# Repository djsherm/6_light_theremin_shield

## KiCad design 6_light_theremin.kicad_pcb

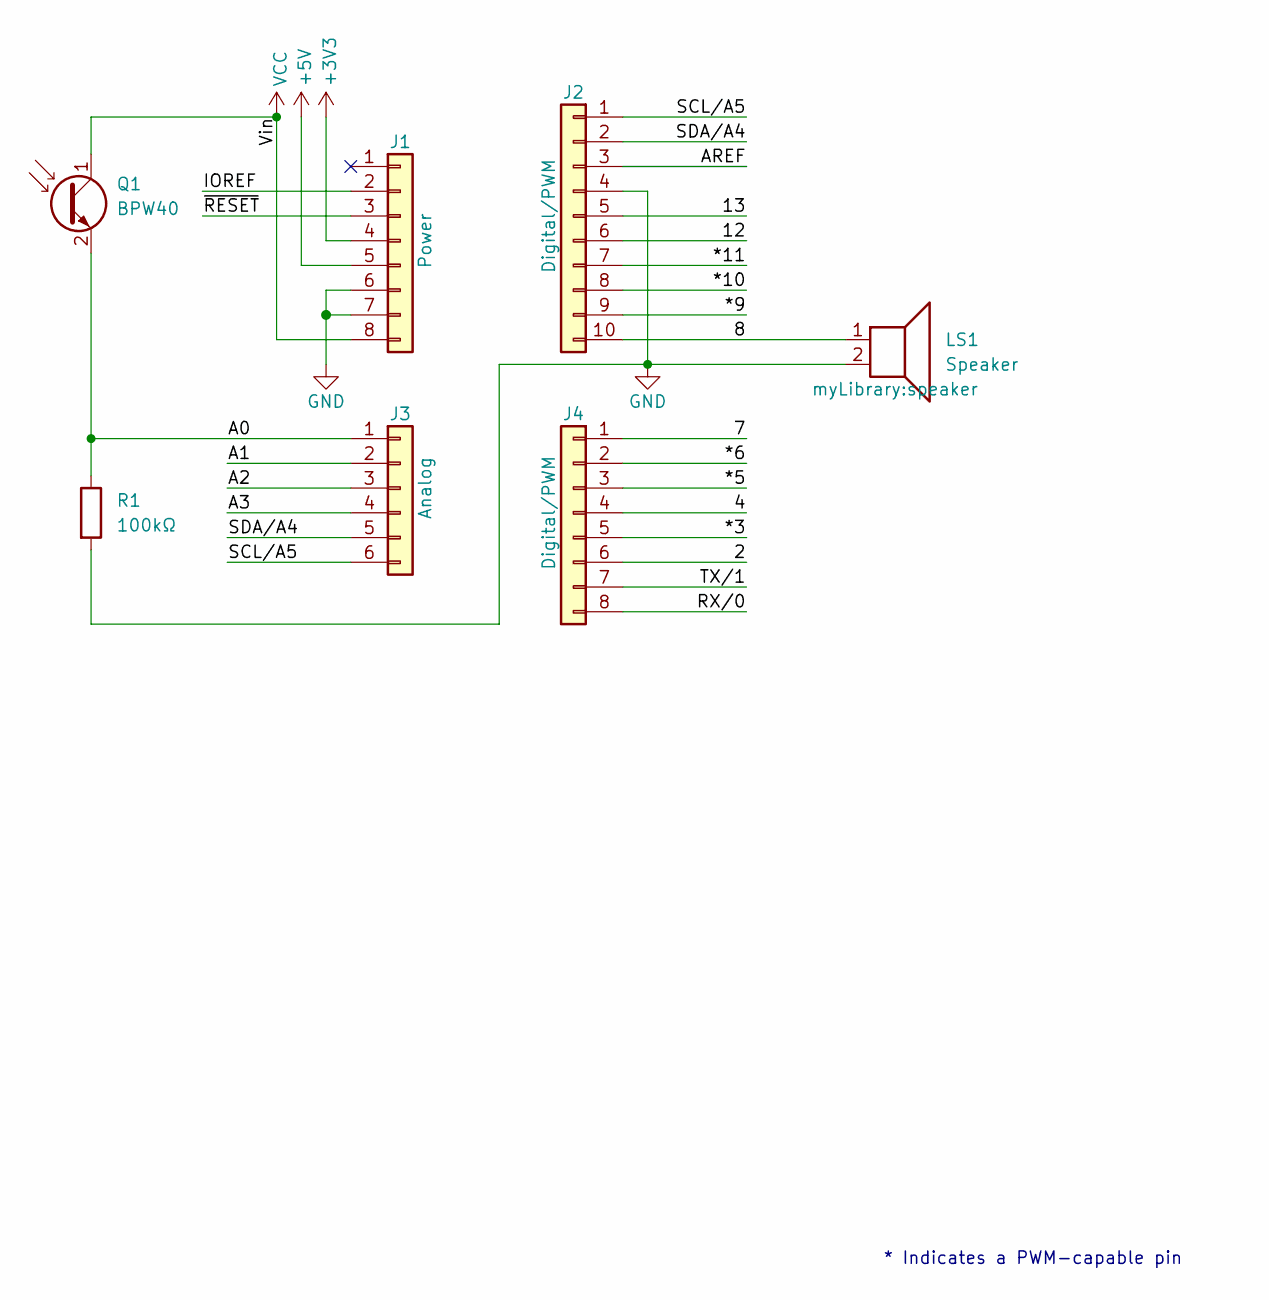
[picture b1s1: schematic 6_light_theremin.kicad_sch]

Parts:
J1: Power; PinSocket_1x08_P2.54mm_Vertical
J2: Digital/PWM; PinSocket_1x10_P2.54mm_Vertical
J3: Analog; PinSocket_1x06_P2.54mm_Vertical
J4: Digital/PWM; PinSocket_1x08_P2.54mm_Vertical
LS1: Speaker; speaker
Q1: BPW40; LED_D5.0mm_Clear
R1: 100kΩ; R_Axial_DIN0207_L6.3mm_D2.5mm_P10.16mm_Horizontal

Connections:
+3V3: J1.4
+5V: J1.5
/2: J4.6
/4: J4.4
/7: J4.1
/8: J2.10, LS1.1
/12: J2.6
/13: J2.5
/*3: J4.5
/*5: J4.3
/*6: J4.2
/*9: J2.9
/*10: J2.8
/*11: J2.7
/A0: J3.1, Q1.2 (E), R1.1
/A1: J3.2
/A2: J3.3
/A3: J3.4
/AREF: J2.3
/IOREF: J1.2
/RX/0: J4.8
/SCL/A5: J2.1, J3.6
/SDA/A4: J2.2, J3.5
/TX/1: J4.7
/~RESET: J1.3
GND: J1.6, J1.7, J2.4, LS1.2, R1.2
VCC: J1.8, Q1.1 (C)

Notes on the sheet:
* Indicates a PWM-capable pin

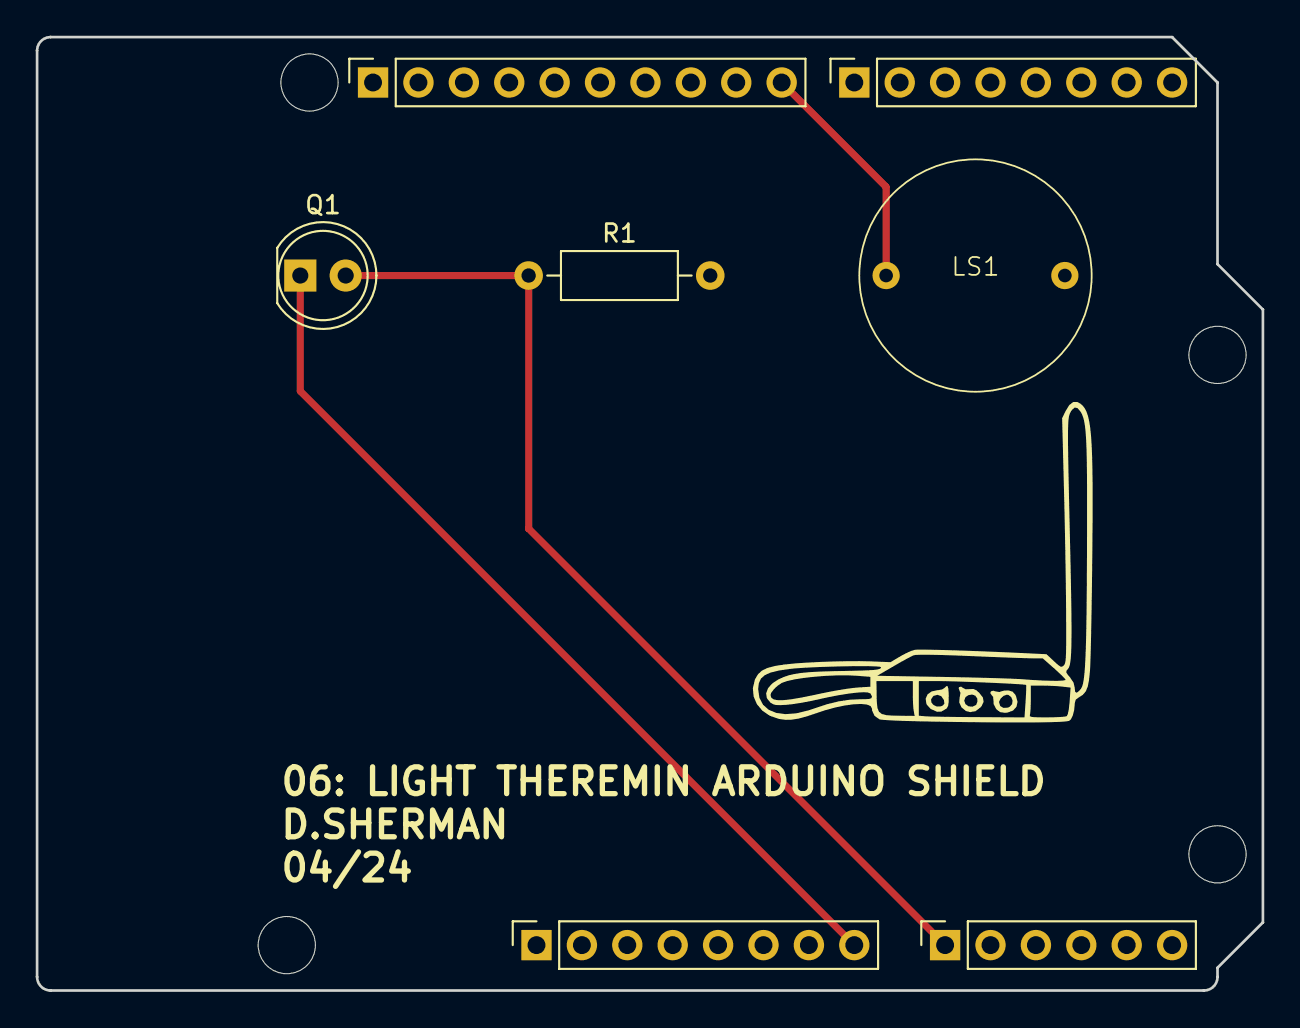
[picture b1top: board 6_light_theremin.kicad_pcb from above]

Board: 2 copper layers, 68.6 x 53.3 mm, 11 parts (0 on the bottom side), 6 nets.

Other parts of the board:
MH1, MH2, MH3, MH4: MountingHole_3.2mm
